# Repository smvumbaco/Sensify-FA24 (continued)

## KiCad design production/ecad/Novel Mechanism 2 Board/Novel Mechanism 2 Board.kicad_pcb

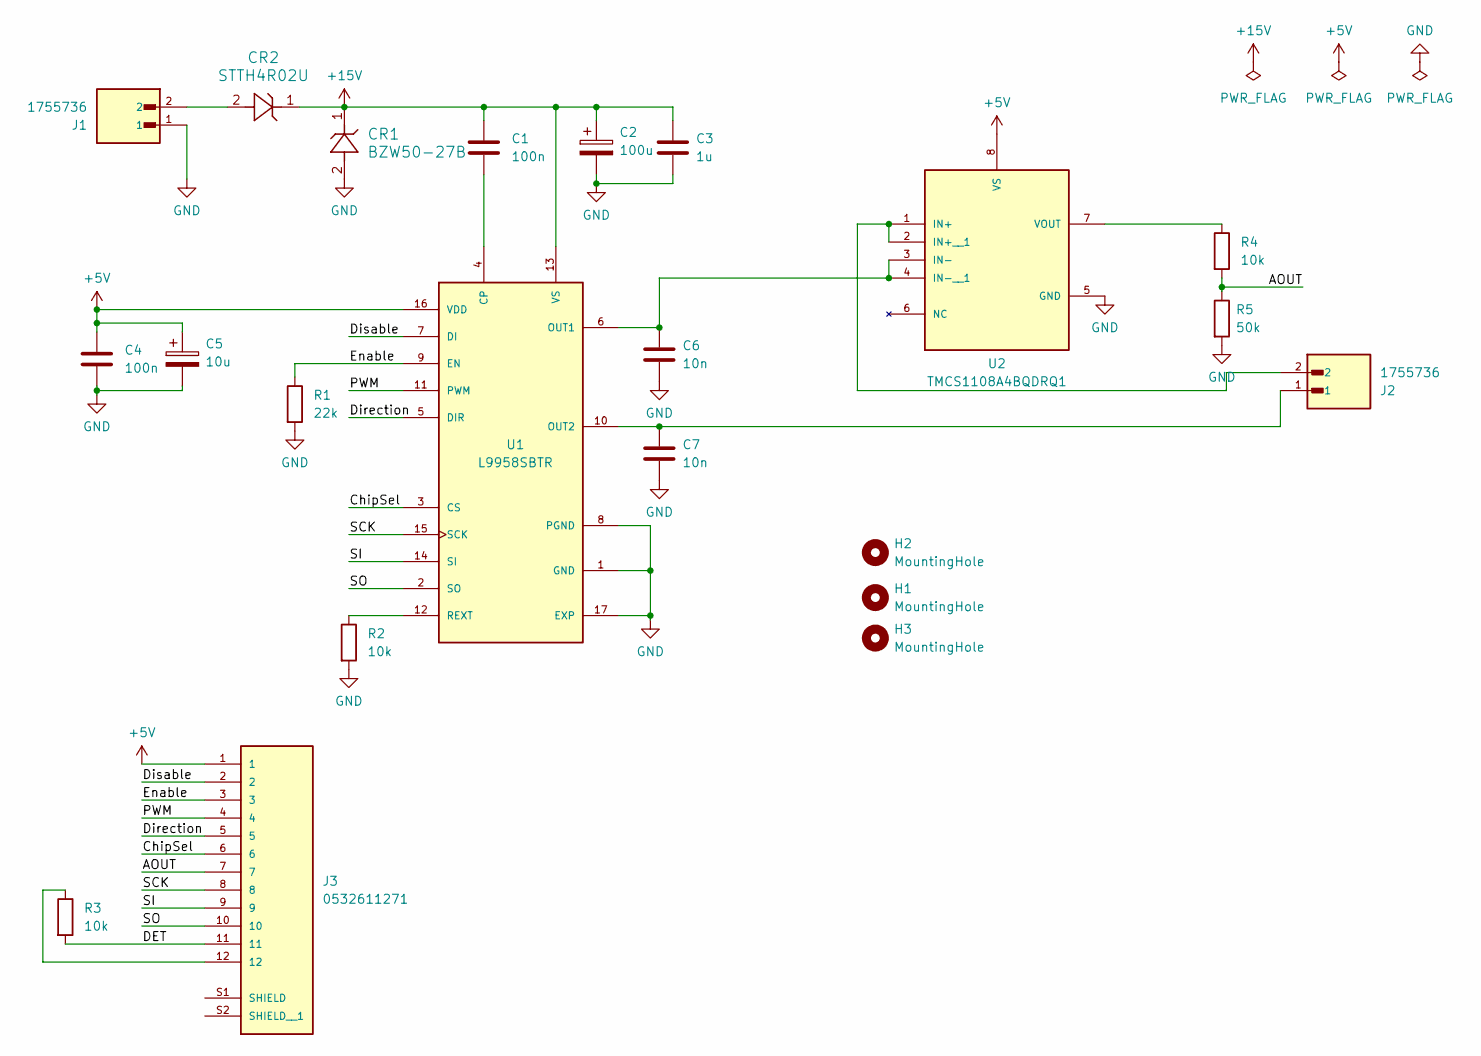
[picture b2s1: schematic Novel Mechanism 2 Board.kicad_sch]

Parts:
C1, C4: 100n; CAP_0603
C2: 100u; EDK107M063A9PAA
C3: 1u; CAP_0603
C5: 10u; EDK106M050A9GAA
C6, C7: 10n; CAP_0603
CR1: BZW50-27B
CR2: STTH4R02U
H1, H2, H3: MountingHole; MountingHole_3.2mm_M3
J1, J2: 1755736; PHOENIX_1755736; PARTREV 11.07.2018
J3: 0532611271; MOLEX_0532611271; PARTREV J
R1: 22k; RES_0603
R2, R3, R4: 10k; RES_0603
R5: 50k; RES_0603
U1: L9958SBTR; SOP80P1410X360-17N; PARTREV 6
U2: TMCS1108A4BQDRQ1; PARTREV July 2021

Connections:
+5V: C4.1, C5.1, J3.1, U1.16 (VDD), U2.8 (VS)
+15V: C1.1, C2.1, C3.1, CR1.1, CR2.1, U1.13 (VS)
/AOUT: J3.7, R4.2, R5.1
/ChipSel: J3.6, U1.3 (CS)
/DET: J3.11, R3.2
/Direction: J3.5, U1.5 (DIR)
/Disable: J3.2, U1.7 (DI)
/Enable: J3.3, R1.1, U1.9 (EN)
/PWM: J3.4, U1.11 (PWM)
/SCK: J3.8, U1.15 (SCK)
/SI: J3.9, U1.14 (SI)
/SO: J3.10, U1.2 (SO)
GND: C2.2, C3.2, C4.2, C5.2, C6.2, C7.2, CR1.2, J1.1, R1.2, R2.2, R5.2, U1.1 (GND), U1.8 (PGND), U1.17 (EXP), U2.5 (GND)
unnamed: CR2.2, J1.2
unnamed: J3.12, R3.1
unnamed: C1.2, U1.4 (CP)
unnamed: C6.1, U1.6 (OUT1), U2.3 (IN-), U2.4 (IN-__1)
unnamed: C7.1, J2.1, U1.10 (OUT2)
unnamed: R2.1, U1.12 (REXT)
unnamed: J2.2, U2.1 (IN+), U2.2 (IN+__1)
unnamed: R4.1, U2.7 (VOUT)

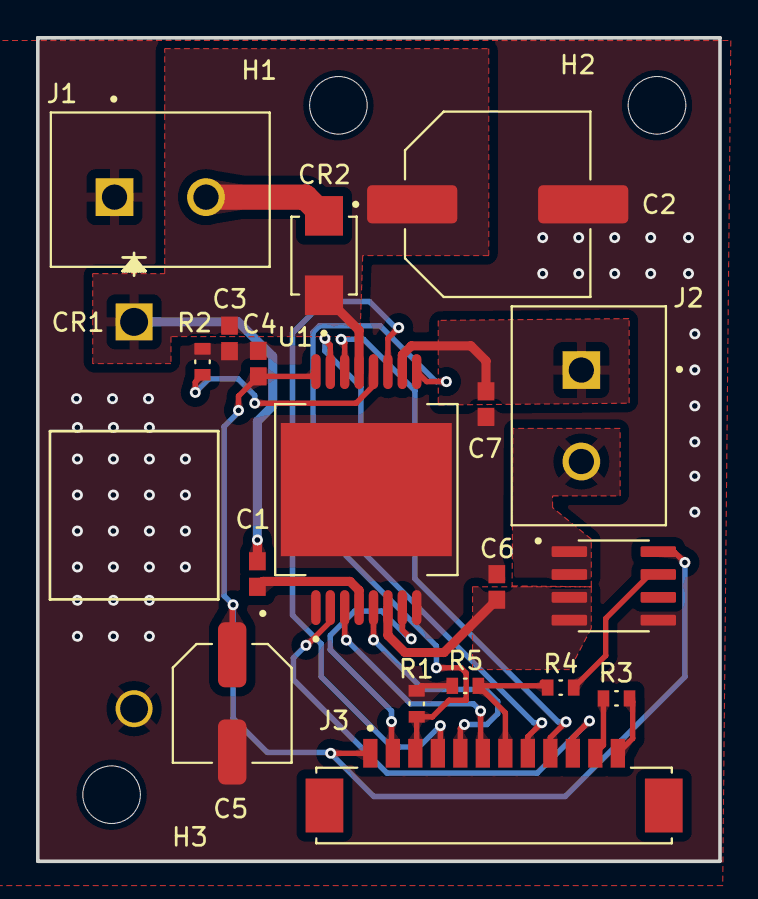
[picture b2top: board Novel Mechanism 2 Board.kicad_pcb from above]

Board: 2 copper layers, 37.9 x 45.8 mm, 22 parts (0 on the bottom side), 21 nets.

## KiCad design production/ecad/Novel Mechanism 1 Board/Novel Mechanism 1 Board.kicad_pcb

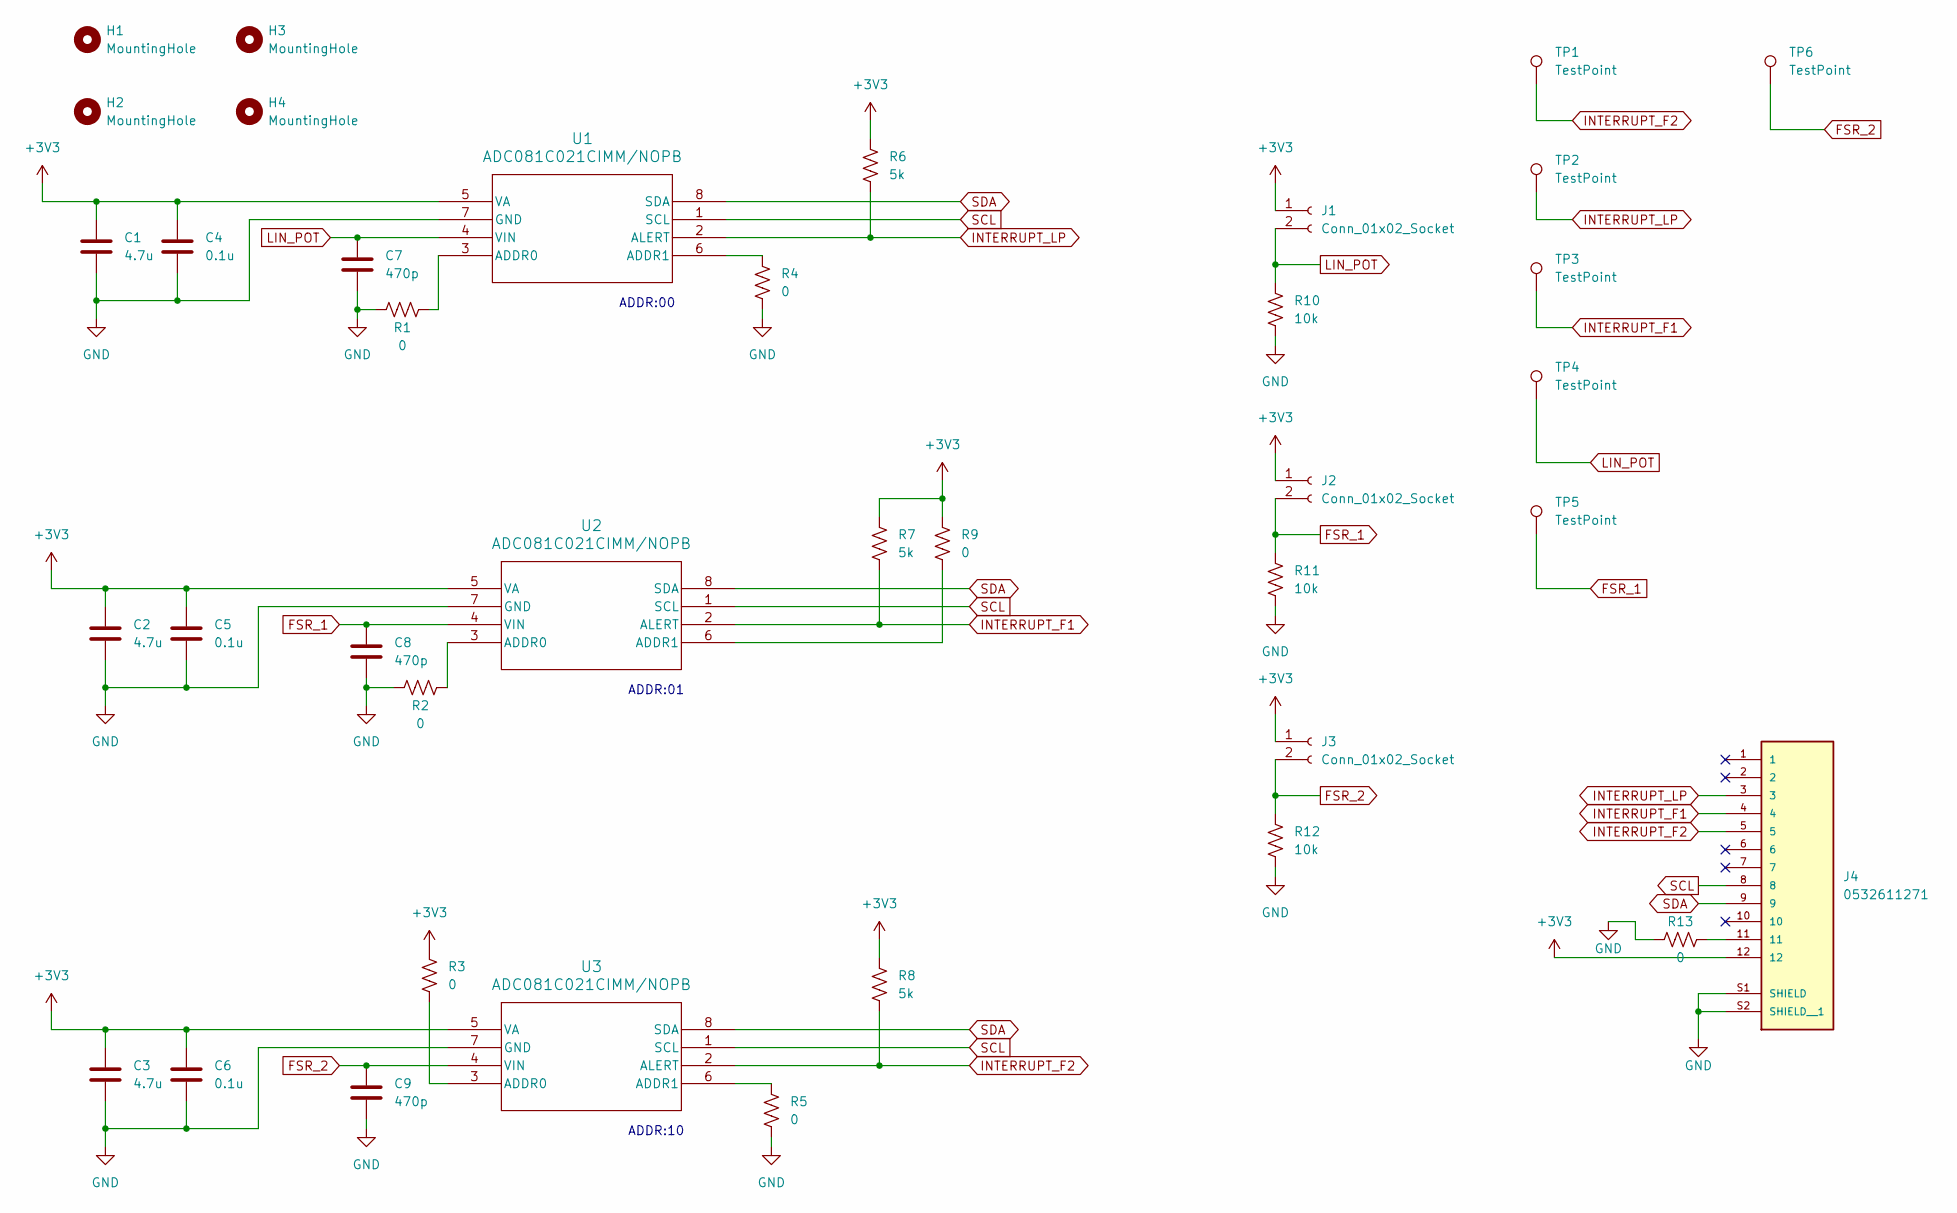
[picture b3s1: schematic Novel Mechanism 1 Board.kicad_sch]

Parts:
C1, C2, C3: 4.7u; C_0402_1005Metric
C4, C5, C6: 0.1u; C_0402_1005Metric
C7, C8, C9: 470p; C_0402_1005Metric
H1, H2, H3, H4: MountingHole; MountingHole_3.2mm_M3
J1, J2, J3: Conn_01x02_Socket; PinHeader_1x02_P2.54mm_Vertical
J4: 0532611271; MOLEX_0532611271; PARTREV J
R1, R2, R3, R4, R5, R9, R13: 0; R_0402_1005Metric
R6, R7, R8: 5k; R_0402_1005Metric
R10, R11, R12: 10k; R_0402_1005Metric
TP1, TP2, TP3, TP4, TP5, TP6: TestPoint; TestPoint_Pad_D2.0mm
U1, U2, U3: ADC081C021CIMM/NOPB; NM-ADC8BIT

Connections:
+3V3: C1.1, C2.1, C3.1, C4.1, C5.1, C6.1, J1.1, J2.1, J3.1, J4.12, R3.1, R6.1, R7.1, R8.1, R9.2, U1.5 (VA), U2.5 (VA), U3.5 (VA)
FSR_1: C8.1, J2.2, R11.1, TP5.1, U2.4 (VIN)
FSR_2: C9.1, J3.2, R12.1, TP6.1, U3.4 (VIN)
GND: C1.2, C2.2, C3.2, C4.2, C5.2, C6.2, C7.2, C8.2, C9.2, J4.S1 (SHIELD), J4.S2 (SHIELD__1), R1.1, R2.1, R4.2, R5.2, R10.2, R11.2, R12.2, R13.1, U1.7 (GND), U2.7 (GND), U3.7 (GND)
INTERRUPT_F1: J4.4, R7.2, TP3.1, U2.2 (ALERT)
INTERRUPT_F2: J4.5, R8.2, TP1.1, U3.2 (ALERT)
INTERRUPT_LP: J4.3, R6.2, TP2.1, U1.2 (ALERT)
LIN_POT: C7.1, J1.2, R10.1, TP4.1, U1.4 (VIN)
unnamed: J4.11, R13.2
unnamed: R1.2, U1.3 (ADDR0)
unnamed: R4.1, U1.6 (ADDR1)
unnamed: R2.2, U2.3 (ADDR0)
unnamed: R9.1, U2.6 (ADDR1)
unnamed: R3.2, U3.3 (ADDR0)
unnamed: R5.1, U3.6 (ADDR1)
SCL: J4.8, U1.1 (SCL), U2.1 (SCL), U3.1 (SCL)
SDA: J4.9, U1.8 (SDA), U2.8 (SDA), U3.8 (SDA)

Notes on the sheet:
ADDR:01
ADDR:00
ADDR:10

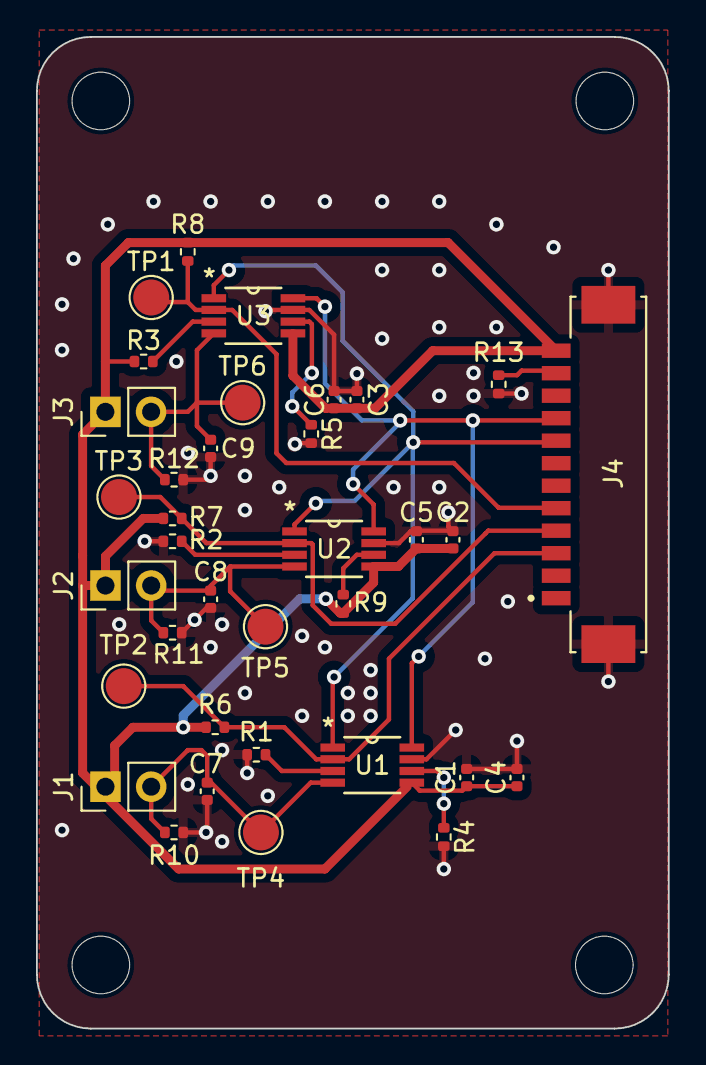
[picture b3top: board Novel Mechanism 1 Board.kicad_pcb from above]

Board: 2 copper layers, 35.1 x 55.1 mm, 39 parts (0 on the bottom side), 17 nets.

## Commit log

2024-09-16 "MainBoard PCB Folder"
2024-09-18 Added Schematic and Layout file for Main Board
2024-09-19 Reset Repo post Workshop
2024-09-19 Added Main Board, BMS, and MCU Schematics Pages
2024-09-19 Changed MCU File Name
2024-09-20 Added Haptics kicad file to main board
2024-09-20 Added Novel Mechanism Boards
2024-09-28 step, mod, sym files for ESP32-WROOM-32, imported into schematic
2024-09-28 started schematic
2024-10-01 added symbols/footprints/3D files for BMIC, 3.3V & 5V LDO
2024-10-01 rough draft for BMS schematic
2024-10-01 mostly done schematic i think. having trouble finding some parts
2024-10-01 added driver ic to components folder
    a
2024-10-01 added driver ic to schematic
2024-10-01 schematic continued
2024-10-01 updated schematic
2024-10-04 adding hierarchical labels
2024-10-04 schematic rough draft
2024-10-04 schematic roug h draft
2024-10-04 Novel Mech 1 Commit
    updated schematic, added components to libraries
2024-10-05 power port and zener added
2024-10-06 draft complete, need to test variable speed trigger before adding to schematic
2024-10-07 adding level shifter
2024-10-07 adding USB to UART
2024-10-08 Footprints
    updated footprints and datasheets
2024-10-09 added footprint
2024-10-09 footprint/datasheet
2024-10-09 Imported Sheet Pins
2024-10-11 IMU
    Added an IMU sheet and connected IMU to stuff
2024-10-11 added to BMS schematic
2024-10-11 added datasheet to ic
2024-10-11 adding platform IO project folder into src folder
2024-10-11 added BMS symbol/footprint libraries + 5v buck and charger IC ecad
2024-10-11 first draft of BMS schematic
2024-10-11 test commit 2
2024-10-11 include this, include that, include a fist in your face
2024-10-14 added electrolytic caps
2024-10-14 added capacitor and resistor footprints
2024-10-14 nothing?
2024-10-15 fixed erc errors
2024-10-15 Added Testing Folders for Firmware
2024-10-16 schematic but V coming in clutch
2024-10-16 added signals to other parts
2024-10-17 New MCU
2024-10-17 Added new 8 bit ADCs
    changing ADCs on the vise mechanism
2024-10-17 Changed ADC
    converted ADC to 8 pin ADC, need to check footprint and add connector
2024-10-18 added passives footprints & changed 5.5V to 5V
2024-10-18 changed addresses
    changed addresses
2024-10-18 changed 10 to 12 pin connector
2024-10-18 added connector
    added connector
2024-10-18 Finalized MCU
2024-10-18 started code
2024-10-18 code in testing folder
2024-10-19 added text for inter module conection
2024-10-21 initial ideas written down for state machine and attachment class setup, I2C bus configurations just about done.
2024-10-22 schematic fixes
2024-10-22 preliminary component placement
2024-10-22 NM1 Schematic Update
    Updated footprints, added footprints to passives, modified some datasheets
2024-10-22 Net Changes
    changed up some net names and added hierarchical labels
2024-10-23 added connectors
2024-10-24 "Improved MCU Schematic"
2024-10-24 added more code
    the haptics_testing file is code of basic library of the waveform stuff from Adafruit, I'm just going to keep it there for future reference - the haptics file is the file where i am ACTIVELY working 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
2024-10-24 Added Novel Mechanism Connection
2024-10-24 my computer got fried but I remembered everything I did
2024-10-24 Added switch footprints for MCU
2024-10-24 some HID code, not tested, trying to figure out how to flash to esp32 on linux 20.04 and having trouble
2024-10-25 Improved MCU Schematic
2024-10-25 Finished Root Directory for IMU and Haptics
2024-10-25 Added Mounting Holes
2024-10-25 Finished IMU, Haptics, MCU, and Root Page
2024-10-25 changed footprint path
2024-10-25 connectors footprint
2024-10-26 Added Test Point footprints, fixed Haptics footprints, fixed IMU footprints
2024-10-26 Footprints and Lables
    modified input/output labels, modified footprint libraries. Sensify Footprints now points to the general footprint library that all of us have been tossing footprints into
2024-10-26 Added footprints for mounting holes
2024-10-27 connector and labels
    updated i/o net labels, added connector from MCU schematic
2024-10-27 Added IO Sheet
2024-10-27 Deleted IO
2024-10-27 Finished Schematic for Vise Mechanism
2024-10-27 Added Test Points and Mounting Holes for Vise Mechanism
2024-10-27 Forgot Testpoint Footprints lol
2024-10-27 Started Layout for Vise Mechanism
2024-10-28 added BMS ecad for v1
2024-10-28 v1 bms ic without charging while using functionality + changed bms hierarchical net labels
2024-10-28 Updated MCU Schematic
2024-10-28 Added Labels to Test Points
2024-10-28 added ALERT pin mosfet footprint
2024-10-29 added fet footprint to schematic + global labels + removed repeat TPs
2024-10-29 fixed BMS schematic merging issues
2024-10-29 added hall effect sensor to components folder
2024-10-29 added hall effect current sense for adc output to microcontroller
2024-10-29 added component to layout
2024-10-29 basically final component placement
2024-10-29 added C16 footprint BMS
2024-10-29 updated footprints for U3, U4
2024-10-29 reannotated REFDES
2024-10-29 added Q2 Q3 footprint BMS
2024-10-29 design rules - main board
2024-10-30 changed pin 10 to not ground
2024-10-30 added correct connector
2024-10-30 added kill switch to BMS
2024-10-31 added resistor divider at aout to fit within microcontroller adc range
2024-10-31 started main board layout
2024-10-31 continuing layout for main board
2024-10-31 imported updated schematic
2024-10-31 updated footprint
2024-11-01 edge cuts
2024-11-01 layout
2024-11-01 continued main board layout
2024-11-01 added switch footprint and symbol
2024-11-01 main board layout
    rerouted the 5V buck supply according to TI guidelines
2024-11-01 Routed most of USB-UART
2024-11-01 placed BMS components minus TPs
2024-11-01 main board
    routed haptics, modified 3.3V supply
2024-11-01 Finished USB to UART Routing
2024-11-01 Deleted routing for USB to UART to allow more flexibility
2024-11-02 main board layout
    finished placing and routing BMS. pours/fills need to be filled in, hasn't been working for me
2024-11-02 Changed Resisitor Footprints
2024-11-02 UART Routing
2024-11-02 HID still sucks
2024-11-03 slightly smaller switch added
2024-11-03 smaller switch
2024-11-03 smaller switch schematic edit
2024-11-03 smaller bms alert pushbutton +fixed reference designators + imu and haptics routing + tried to make stuff closer together
2024-11-03 put in TPs + haptics half placed + tried to fit stuff in more
2024-11-04 novel mech 1 layout
2024-11-04 Revert "novel mech 1 layout"
    This reverts commit bfcc3e9fe9e6e44316e63a68225a0cfb2712f792.
2024-11-04 Finished UART, Haptics, and IMU
2024-11-04 Reapply "novel mech 1 layout"
    This reverts commit 0a2fee7e23d52c75885e70a076fd6c2b58554b93.
2024-11-04 changed tp names + attempted to start placing mcu and making space for mounting holes?
2024-11-04 updated design constraints
2024-11-04 signal routing complete!
2024-11-04 preliminary copper zones
2024-11-04 main board layout
    made some changes to routing, connected up parts of the MCU
2024-11-04 added last mounting hole and moved aronud R7 to make room for MH
2024-11-04 Main Board Layout
2024-11-05 routing generally done
2024-11-05 mounting holes...
2024-11-05 Everything UART and above is error free
2024-11-05 Under 6 No Connections, less than 100 DRC errors...
2024-11-05 routing complete - preteardrops
2024-11-05 teardrops added
2024-11-05 Down to 32 DRC Errors
2024-11-05 fixed silkscreen
2024-11-05 fixed errors
    edited pours to be traces, fixed clearance issues, SOLDERMASK ERRORS STILL EXIST
2024-11-05 resolving errors
2024-11-05 removed unnecessary back routing
2024-11-05 Tried some silk screen bullshit...
2024-11-05 63 errors
2024-11-05 15 DRC errors
2024-11-06 Board
2024-11-06 Billy first look
2024-11-06 clearance errors
2024-11-06 bluetooth code flashes and works properly, if we went with this option, we would need to get python package for vjoy working to translate data into HID input
2024-11-06 gamepad library allows for persistent connection, now we have to figure out how we are going to send data as button presses and joystick axes...
2024-11-06 0 errors yay
2024-11-06 Fixed USB to UART diff pair
2024-11-06 Mini Changes
2024-11-06 bms firmware initial commit
2024-11-06 power pours + ground pours
2024-11-06 Set all GND pours to priority 0
2024-11-07 thickened u3 3v3 trace
2024-11-07 Diff Pair track lengths are the same
2024-11-07 Finalized Silkscreen
2024-11-07 HUGE updates lets go babyyyy
    way too easy
2024-11-07 final board edits
2024-11-08 Added LCSC parts to KiCAD
2024-11-08 put bms code in testing folder
2024-11-08 added jlc part numbers
2024-11-08 added mosfet for load switch to bms + adjusted layout accordingly + fixed outdated ref degs
2024-11-08 added JLC part numbers to main board
2024-11-08 added JLC part numbers for main board spreadsheet
2024-11-08 Deleted CSV
2024-11-08 Novel Mech 2 JLC files complete
2024-11-08 Finished files for Novel Mech 1
2024-11-08 Removed Errors
2024-11-08 Finished files for Main Board JLC
2024-11-08 New File Setup Main Board
2024-11-08 Finalized Novel Mech 1 Files
2024-11-08 Novel Mech 2 Files Finalized
2024-11-08 Fixed All files please work
2024-11-13 small changes before meeting 11/12
2024-11-13 added more 3D models
2024-11-13 add more 3D models
2024-11-15 spi.h for Hari to look at
2024-11-15 changed spi setting frequency and created pwm function
2024-11-15 haptics firmware
2024-11-18 spi library file messed with compilation so I removed it, added packet scheme for sending over bluetooth, on receiving end we receive a packet and can print it out (still need to figure out how to on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
2024-11-20 Vise Code
    changed addresses
2024-11-21 imu function should be done
2024-11-30 added BMS IC read and write functionality
